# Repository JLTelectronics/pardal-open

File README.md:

<div align="center">

### Speed, speed cameras, matrix signs and road alerts from official open sources
**No account · No ads · No trip history**

-111)

</div>

---

Pardal is a calm co-pilot for the car. It shows your speed and the limit, warns you for speed cameras,
matrix signs and incidents on the road, and lets drivers warn each other — all from official open data,
without an account, without ads and without keeping track of where you drive.

<div align="center">

<table border="0" cellpadding="8">
<tr>
<td align="center"></td>
<td align="center"></td>
<td align="center"></td>
<td align="center"></td>
</tr>
<tr>
<td align="center" width="205"><sub>The meter at the top, and below it everything coming your way on the road.</sub></td>
<td align="center" width="205"><sub>Navigation with spoken directions, arrival time and the road's limit.</sub></td>
<td align="center" width="205"><sub>The map across the whole screen, with a large REPORT button.</sub></td>
<td align="center" width="205"><sub>Navigating between real buildings with their height from 3D BAG.</sub></td>
</tr>
</table>

</div>

## Why Pardal?

Speed-camera and traffic apps have grown ever more crowded, more expensive and more nosy:
subscriptions, accounts, ads and extensive tracking. Pardal is the opposite — a calm
co-pilot that does exactly what is needed and otherwise leaves you in peace.

| | |
|---|---|
| 🟠 **Useful from the very first metre** | The basics come from official open government data, so it is useful right away — even without a large user base. |
| 🟠 **Privacy by design** | No account, no trip history. Shared reports use a rotating, hashed device ID and a position rounded to ~1 km. |
| 🟠 **Calm on screen** | One clear meter, one quiet beep. Nothing that flashes or pops up unless your safety requires it. |
| 🟠 **Open and self-hostable** | The server, the hardware and the boot system are open source. |

## Features

| | |
|---|---|
| **Speed** | Large meter with the applicable limit; a calm warning when you go too fast. |
| **Speed cameras** | Fixed cameras, average-speed (section) controls and ANPR from OpenStreetMap. |
| **Matrix signs** | Live speeds and red crosses (lane closures) from NDW/Rijkswaterstaat. |
| **Road alerts** | Traffic jams, accidents, roadworks, closures and open bridges. |
| **Weather** | KNMI warnings along the way. |
| **Report it yourself** | Police, traffic jam, accident and more — visible to others after three confirmations. |
| **Navigation** | Address search, spoken directions in six languages and automatic re-routing. |
| **Offline map** | 2D/3D map from the Rijkswaterstaat road dataset; no data usage on the road. |
| **Multilingual** | Nederlands, English, Deutsch, Español, Português and Frysk. Light/dark theme. |

Full description: **[docs/FUNCTIES.md](docs/FUNCTIES.md)**.

## Where does it run?

| Platform | Status | |
|---|---|---|
| **iPhone** | ✅ Available, including **CarPlay** | [**Download on the App Store →**](https://apps.apple.com/nl/app/pardal/id6836411492) |
| **Android** | 🚧 On the way, including **Android Auto** | Coming to Google Play |
| **Dedicated car display** | 🚧 Open hardware in development | See [`hardware/`](hardware) and [the end of this page](#running-pardal-on-a-dash01) |

> The Pardal **apps** (iOS, Android) are proprietary and not part of this repository. This repository
> contains the open **server**, **hardware** and **DASH boot system**.

## Privacy

- No account, no ads, no analytics from third parties.
- Your location stays on your device. Only when you share a report does a position go to the server,
  rounded to ~1 km and kept in memory only.
- Device IDs are random and stored hashed; a report becomes visible to others only after three
  independent confirmations.

Details: [privacy statement](docs/play/privacyverklaring.md).

## Data sources

Rijkswaterstaat (WKD, matrix signs), NDW (traffic alerts), KNMI (weather) and OpenStreetMap
(speed cameras, roads) — supplemented with open data from several European countries. Details in
[docs/FUNCTIES.md](docs/FUNCTIES.md#data-sources).

## Self-hosting the server

Shared reports, the live map and navigation run through a small, open backend:

```sh
cd server
docker compose up -d --build
```

Configuration and optional receivers: [server/README.md](server/README.md).

## Open hardware

We are designing a round, standalone car display — a "phone without a camera" for the dashboard — with a
bootloader you can **always unlock and recover**. Open KiCad design and a complete bill of materials:
see [`hardware/`](hardware).

## Repository structure

| Folder | Contents |
|---|---|
| [`server/`](server) | Self-hostable backend (FastAPI + SQLite): shared reports, live map, navigation, app configuration. |
| [`hardware/`](hardware) | Open hardware for a round car display: KiCad PCB and bill of materials. |
| [`dash-pure/`](dash-pure) | Boot system and installer for running Pardal on a DASH01. |
| [`docs/`](docs) | Features, server configuration, installation guide and screenshots. |

## Community

Want to think along, help build, or just ride along and report what went wrong? You are welcome.

- 💬 **[Discord](https://discord.gg/HdaQD6NHMN)** — chat, help and ride-alongs
- 🐛 **[GitHub Issues](../../issues)** and **[Discussions](../../discussions)** — questions, ideas, bugs
- 🤝 **[CONTRIBUTING.md](CONTRIBUTING.md)** · **[ROADMAP.md](ROADMAP.md)** — `good first issue` is a nice place to start

---

## Running Pardal on a DASH01

<div align="center">
<table border="0" cellpadding="8">
<tr>
<td align="center"></td>
<td align="center"></td>
<td align="center"></td>
</tr>
</table>
</div>

The Flitsmeister DASH01 is designed to be used with a Flitsmeister subscription. With a small custom boot system and Android 13, your own hardware can run as a standalone on-board computer: **ignition on → Pardal logo → Pardal**, with no detours.

### Connectivity (4G, Wi-Fi & Bluetooth)

Pardal uses standard Android networking for live traffic alerts and map updates. The installer does not touch the built-in eSIM chip. Without an active Flitsmeister subscription, the built-in eSIM profile still shows the network operator but no longer provides mobile data. To get online, choose one of these:

* **Your own data eSIM:** add a data eSIM profile from a provider of your choice.
* **Wi-Fi hotspot:** connect the DASH01 to your phone's personal hotspot.
* **Bluetooth tethering:** share your phone's internet connection over Bluetooth.

Without a connection, Pardal keeps working with the most recently downloaded maps and speed cameras. As soon as it is online again (eSIM, Wi-Fi or Bluetooth), it updates to the latest speed cameras, road alerts and shared reports.

### Your device, your backup

The installer **first makes a complete, verified backup** of your own device and can
restore it to the factory state. **No factory firmware or Flitsmeister software is distributed**
— the installer uses only what is already on your own device, and the Android image (LineageOS GSI)
is downloaded by you from its official source.

→ [Installation guide](docs/DASH01-INSTALLEREN.md) · [How installation works](docs/BOOTLOADER.md) · [`dash-pure/`](dash-pure)

## Independence, trademarks & licence

Pardal is an **independent project**. It is not affiliated with, endorsed by or sponsored by
Flitsmeister or any other company. "Flitsmeister" and "DASH01" are names/trademarks of their
respective owners and are used here only to describe which hardware Pardal can run on.

This repository contains **no** code, firmware, data, APIs or other materials from Flitsmeister.
Installing Pardal on a device you own is your own choice and at your own risk: it can void your
warranty, and the original software and services will not work while Pardal is installed.
The software is provided **without any warranty**, as described in the licence.

### Licences

| Part | Licence |
|---|---|
| [`server/`](server) | [GNU AGPLv3](server/LICENSE) — if you run a modified version as a public service, you must share its source code. |
| [`hardware/`](hardware) | [CERN-OHL-S-2.0](hardware/LICENSE) — modified designs you make or distribute must be published under the same licence. |
| Everything else ([`dash-pure/`](dash-pure), [`docs/`](docs), ...) | [GNU GPLv3](LICENSE) |

Third-party components keep their own licences (see e.g. [`server/app/static/vendor/LICENSES.txt`](server/app/static/vendor/LICENSES.txt)).

The **Pardal name and logo** are not covered by these licences. You may not use them for your own
version or product without permission.

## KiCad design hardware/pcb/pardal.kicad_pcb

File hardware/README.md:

# Pardal hardware

Open hardware for a round, standalone car display: a "phone without a camera" for the dashboard, with a
bootloader you can **always unlock and recover**. Status: in development (rev B), not yet produced.

## Overview
- **Compute:** Radxa CM3 (Rockchip RK3566), Android 11/12 (Treble, GSIs run), open U-Boot.
- **Mobile:** Quectel EC200U-EU (LTE Cat 1 + GNSS), nano-SIM and a soldered eUICC (eSIM).
- **Screen:** round DSI display with touch.
- **Other:** speaker amplifier, vibration motor, side buttons, USB-C (power + data), optional Qi charging.

## Folder layout
| Folder | Contents |
|---|---|
| `pcb/` | KiCad project (`pardal.kicad_pro`), PCB renders and the generator scripts in `pcb/tools/`. |
| `pcb/libs/` | Symbols, footprints and 3D models used by the project. The `lcsc.*` libraries were generated from the LCSC/EasyEDA part library with [easyeda2kicad](https://github.com/uPesy/easyeda2kicad.py). |
| `pcb/datasheets/` | Pin tables (JSON) used by the generator scripts. |
| `pcb/tools/maten.py` | Board size and component positions (mm) used by `gen_pcb.py`. |

## PCB
Open `pcb/pardal.kicad_pro` in KiCad.

- Bill of materials with order numbers: [`pcb/ONDERDELEN.md`](pcb/ONDERDELEN.md).
- Layer stack-up, net classes and routing order: [`pcb/ROUTEREN.md`](pcb/ROUTEREN.md).

The schematic and board outline are generated from code. Run the scripts that use `pcbnew` with KiCad's Python:

```sh
cd pcb
python3 tools/gen_sch.py     # schematic sheets from tools/design.py
python3 tools/gen_pcb.py     # board outline, mounting holes, antenna zones, placement
python3 tools/regels.py      # net classes and design rules
python3 tools/route.py       # optional: autorouting with Freerouting
python3 tools/jlc.py "<part>"   # look up price/stock at JLCPCB/LCSC
```

Datasheets of the modules (Radxa, Quectel, …) are not included: download them from the manufacturers.

## Unlockable and unbrickable by design
- The secure-boot fuses are **never** blown: the chip always accepts your own bootloader.
- **Recovery button** behind a pinhole: hold it at power-on for Rockusb/Loader mode. Empty or broken storage
  falls back to Maskrom automatically. Flash with `rkdeveloptool` over USB-C.
- Debug UART and reset on test points.

See also [docs/BOOTLOADER.md](../docs/BOOTLOADER.md).

## Licence
The hardware design is licensed under the [CERN Open Hardware Licence v2 – Strongly Reciprocal](LICENSE)
(CERN-OHL-S-2.0). Source location: <https://github.com/JLTelectronics/pardal-open/tree/main/hardware>.
The scripts in `pcb/tools/` are part of the design source. The Pardal name and logo are not covered by this licence.

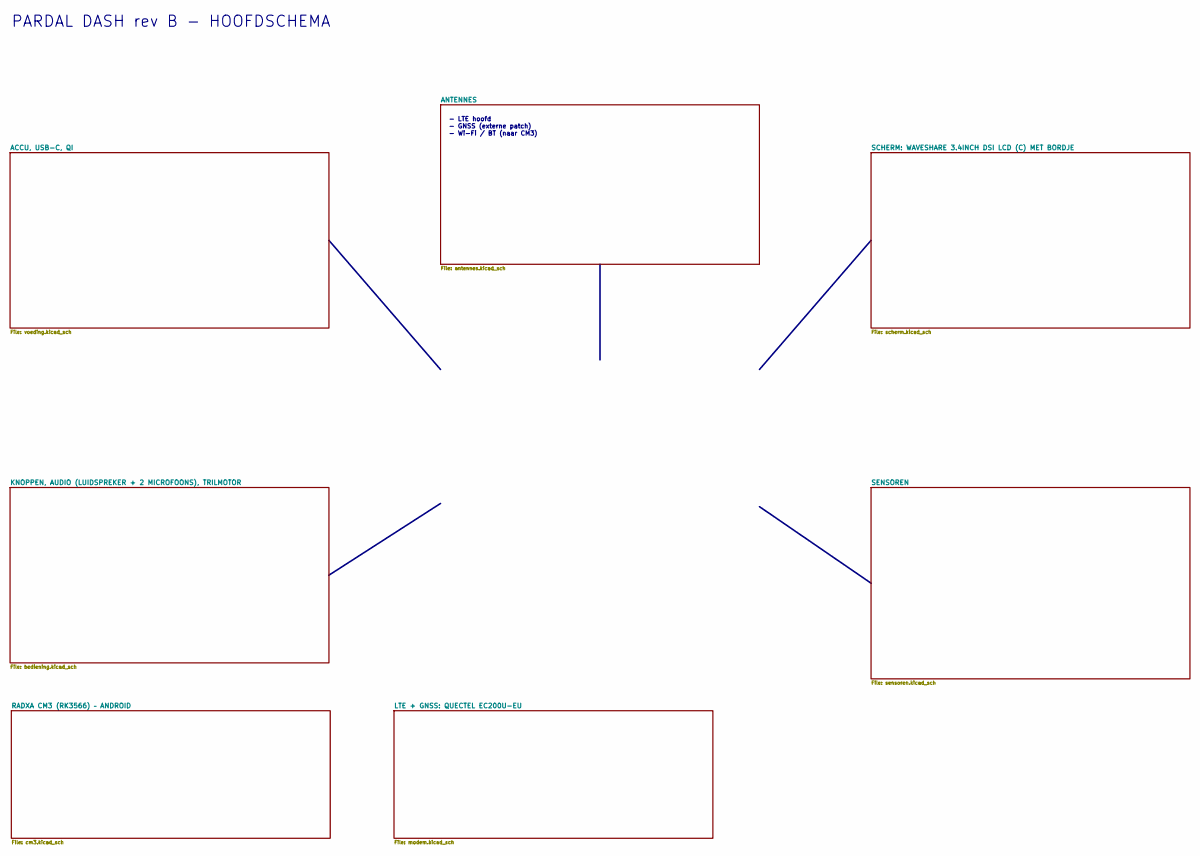
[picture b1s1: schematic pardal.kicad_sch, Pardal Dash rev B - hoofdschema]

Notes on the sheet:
- LTE hoofd - GNSS (externe patch) - Wi-Fi / BT (naar CM3)
PARDAL DASH rev B - HOOFDSCHEMA

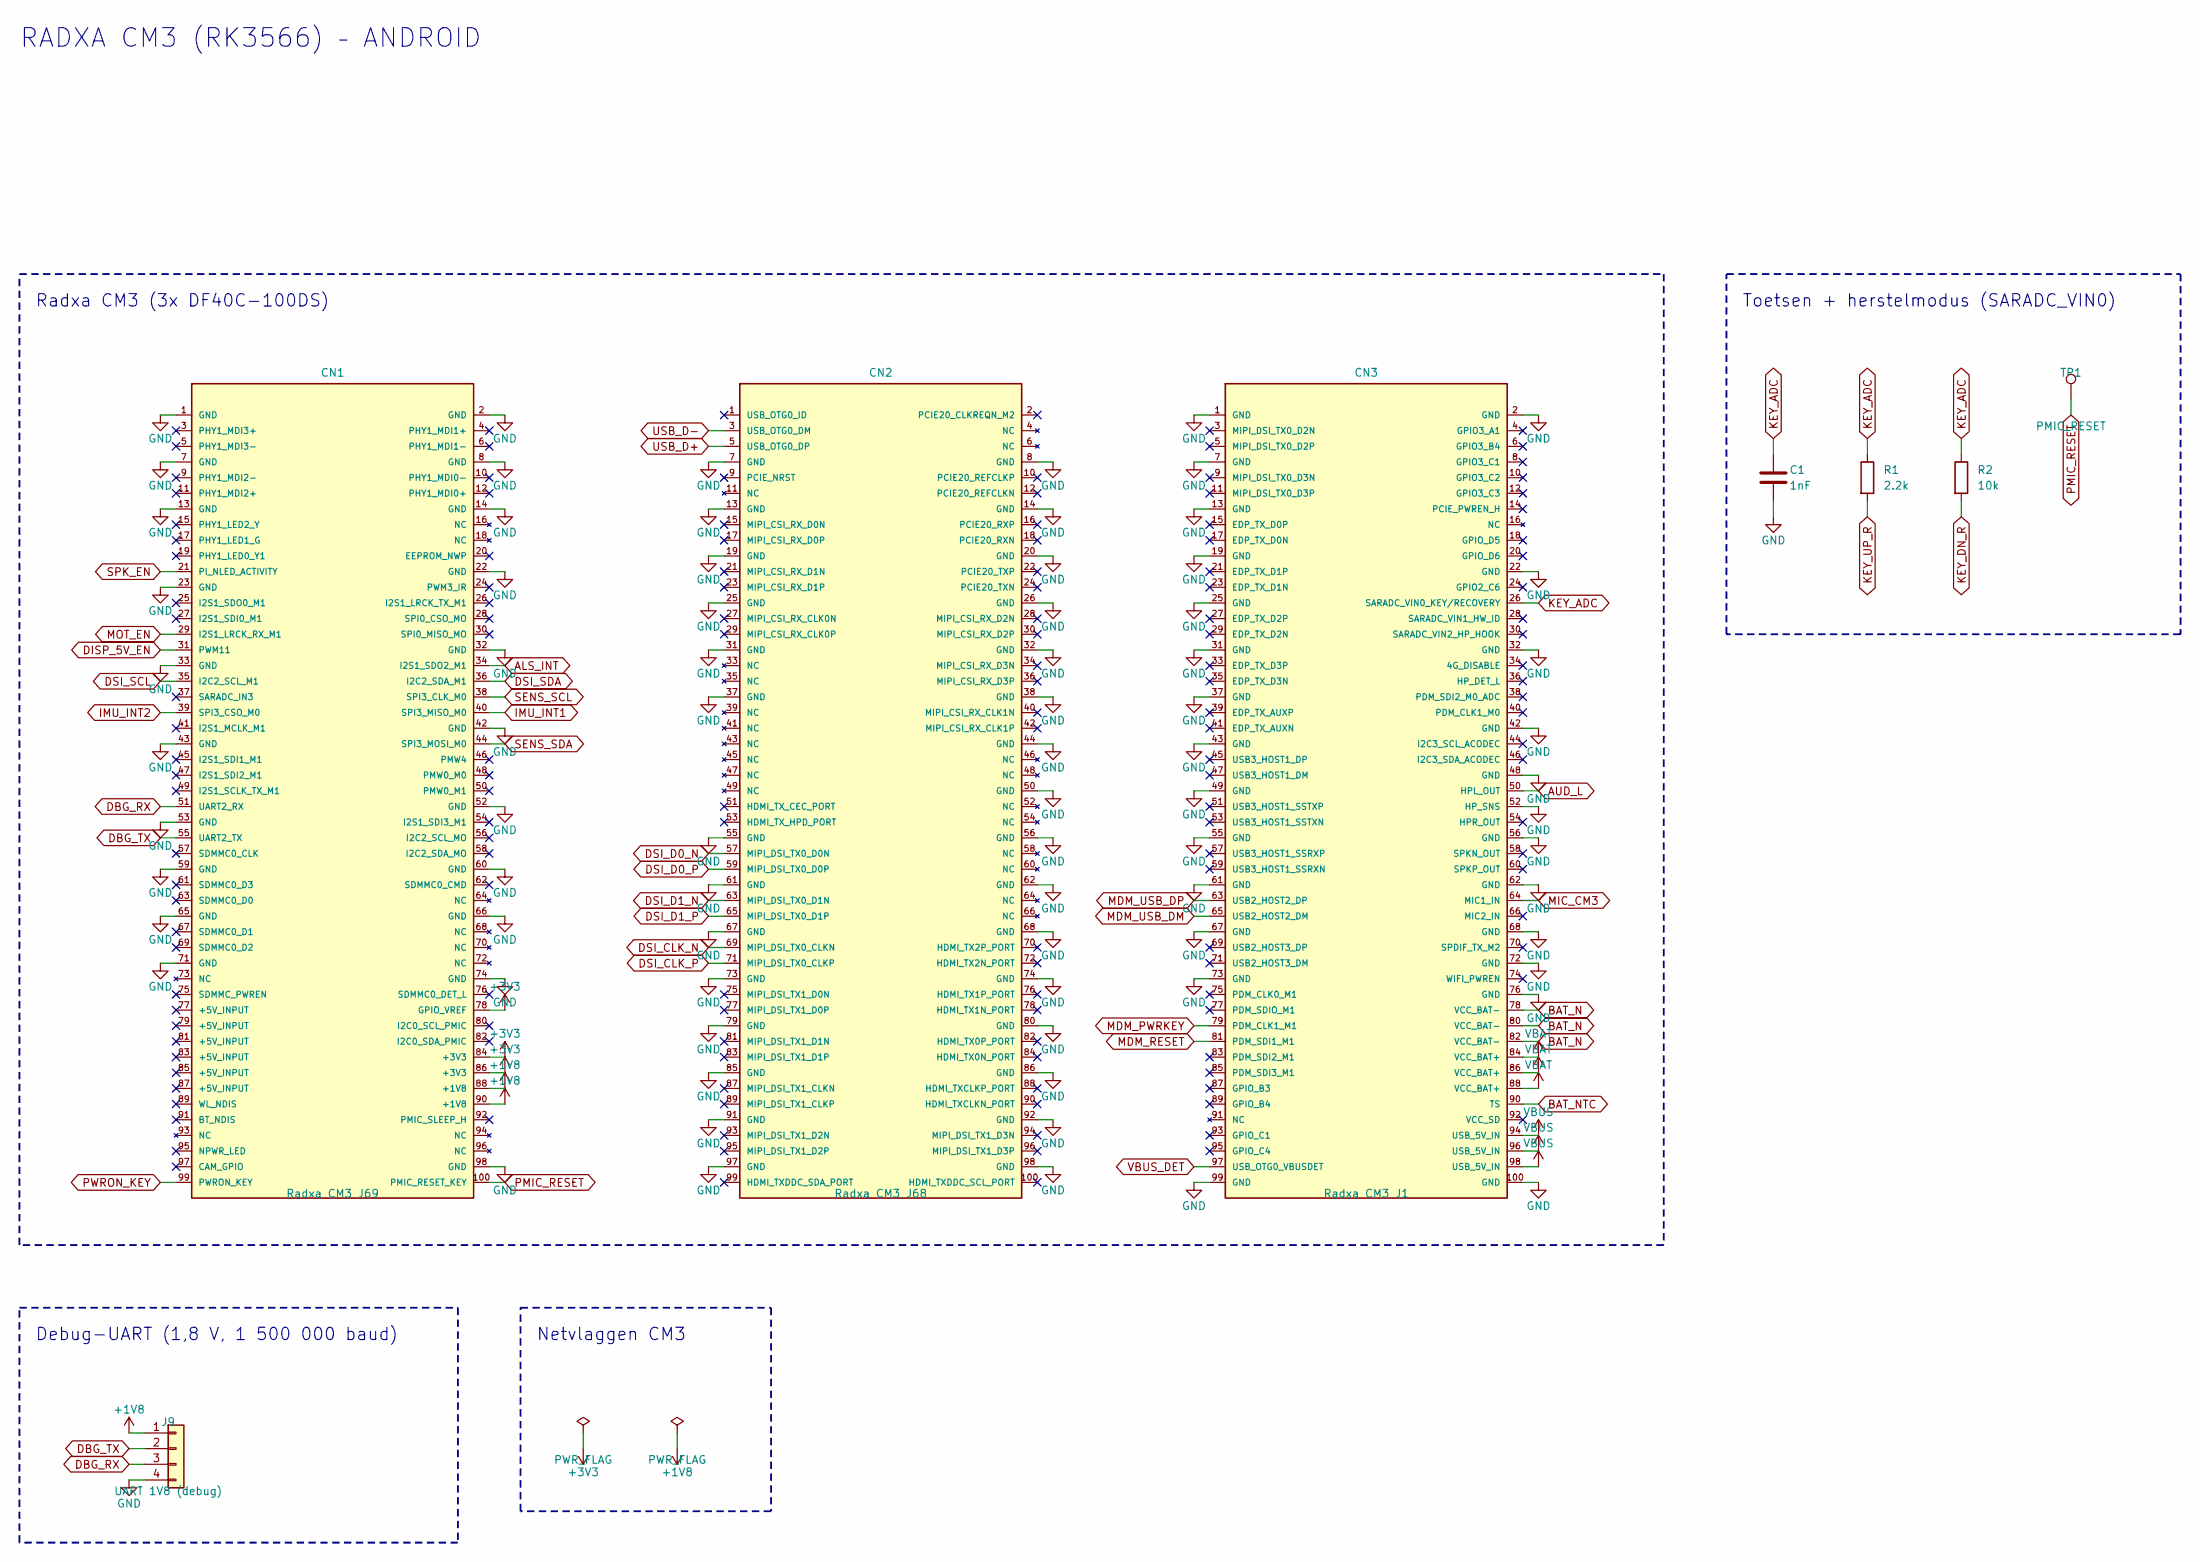
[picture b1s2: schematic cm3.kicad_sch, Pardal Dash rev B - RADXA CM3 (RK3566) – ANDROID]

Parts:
C1: 1nF; C_0402_1005Metric; LCSC C1523
CN1: Radxa CM3 J69; Radxa_CM3_J69; LCSC C597931
CN2: Radxa CM3 J68; Radxa_CM3_J68; LCSC C597931
CN3: Radxa CM3 J1; Radxa_CM3_J1; LCSC C597931
J9: UART 1V8 (debug); UART_4pads_P2.54
R1: 2.2k; R_0402_1005Metric; LCSC C25879
R2: 10k; R_0402_1005Metric; LCSC C25744
TP1: PMIC_RESET; TestPoint_Pad_D1.0mm

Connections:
+1V8: CN1.88 (+1V8), CN1.90 (+1V8), J9.1
+3V3: CN1.78 (GPIO_VREF), CN1.84 (+3V3), CN1.86 (+3V3); also elsewhere on the board
ALS_INT: CN1.34 (I2S1_SDO2_M1); also elsewhere on the board
AUD_L: CN3.50 (HPL_OUT); also elsewhere on the board
BAT_N: CN3.78 (VCC_BAT-), CN3.80 (VCC_BAT-), CN3.82 (VCC_BAT-); also elsewhere on the board
BAT_NTC: CN3.90 (TS); also elsewhere on the board
DBG_RX: CN1.51 (UART2_RX), J9.3
DBG_TX: CN1.55 (UART2_TX), J9.2
DISP_5V_EN: CN1.31 (PWM11); also elsewhere on the board
DSI_CLK_N: CN2.69 (MIPI_DSI_TX0_CLKN); also elsewhere on the board
DSI_CLK_P: CN2.71 (MIPI_DSI_TX0_CLKP); also elsewhere on the board
DSI_D0_N: CN2.57 (MIPI_DSI_TX0_D0N); also elsewhere on the board
DSI_D0_P: CN2.59 (MIPI_DSI_TX0_D0P); also elsewhere on the board
DSI_D1_N: CN2.63 (MIPI_DSI_TX0_D1N); also elsewhere on the board
DSI_D1_P: CN2.65 (MIPI_DSI_TX0_D1P); also elsewhere on the board
DSI_SCL: CN1.35 (I2C2_SCL_M1); also elsewhere on the board
DSI_SDA: CN1.36 (I2C2_SDA_M1); also elsewhere on the board
GND: C1.2, CN1.1 (GND), CN1.2 (GND), CN1.7 (GND), CN1.8 (GND), CN1.13 (GND), CN1.14 (GND), CN1.22 (GND), CN1.23 (GND), CN1.32 (GND), CN1.33 (GND), CN1.42 (GND), CN1.43 (GND), CN1.52 (GND), CN1.53 (GND), CN1.59 (GND), CN1.60 (GND), CN1.65 (GND), CN1.66 (GND), CN1.71 (GND), CN1.74 (GND), CN1.98 (GND), CN2.7 (GND), CN2.8 (GND), CN2.13 (GND), CN2.14 (GND), CN2.19 (GND), CN2.20 (GND), CN2.25 (GND), CN2.26 (GND), CN2.31 (GND), CN2.32 (GND), CN2.37 (GND), CN2.38 (GND), CN2.44 (GND), CN2.50 (GND), CN2.55 (GND), CN2.56 (GND), CN2.61 (GND), CN2.62 (GND), CN2.67 (GND), CN2.68 (GND), CN2.73 (GND), CN2.74 (GND), CN2.79 (GND), CN2.80 (GND), CN2.85 (GND), CN2.86 (GND), CN2.91 (GND), CN2.92 (GND), CN2.97 (GND), CN2.98 (GND), CN3.1 (GND), CN3.2 (GND), CN3.7 (GND), CN3.13 (GND), CN3.19 (GND), CN3.22 (GND), CN3.25 (GND), CN3.31 (GND), CN3.32 (GND), CN3.37 (GND), CN3.42 (GND), CN3.43 (GND), CN3.48 (GND), CN3.49 (GND), CN3.52 (HP_SNS), CN3.55 (GND), CN3.56 (GND), CN3.61 (GND), CN3.62 (GND), CN3.67 (GND), CN3.68 (GND), CN3.72 (GND), CN3.73 (GND), CN3.76 (GND), CN3.99 (GND), CN3.100 (GND), J9.4; also elsewhere on the board
IMU_INT1: CN1.40 (SPI3_MISO_M0); also elsewhere on the board
IMU_INT2: CN1.39 (SPI3_CSO_M0); also elsewhere on the board
KEY_ADC: C1.1, CN3.26 (SARADC_VIN0_KEY/RECOVERY), R1.1, R2.1; also elsewhere on the board
KEY_DN_R: R2.2; also elsewhere on the board
KEY_UP_R: R1.2; also elsewhere on the board
MDM_PWRKEY: CN3.79 (PDM_CLK1_M1); also elsewhere on the board
MDM_RESET: CN3.81 (PDM_SDI1_M1); also elsewhere on the board
MDM_USB_DM: CN3.65 (USB2_HOST2_DM); also elsewhere on the board
MDM_USB_DP: CN3.63 (USB2_HOST2_DP); also elsewhere on the board
MIC_CM3: CN3.64 (MIC1_IN); also elsewhere on the board
MOT_EN: CN1.29 (I2S1_LRCK_RX_M1); also elsewhere on the board
PMIC_RESET: CN1.100 (PMIC_RESET_KEY), TP1.1
PWRON_KEY: CN1.99 (PWRON_KEY); also elsewhere on the board
SENS_SCL: CN1.38 (SPI3_CLK_M0); also elsewhere on the board
SENS_SDA: CN1.44 (SPI3_MOSI_M0); also elsewhere on the board
SPK_EN: CN1.21 (PI_NLED_ACTIVITY); also elsewhere on the board
USB_D+: CN2.5 (USB_OTG0_DP); also elsewhere on the board
USB_D-: CN2.3 (USB_OTG0_DM); also elsewhere on the board
VBAT: CN3.84 (VCC_BAT+), CN3.86 (VCC_BAT+), CN3.88 (VCC_BAT+); also elsewhere on the board
VBUS: CN3.94 (USB_5V_IN), CN3.96 (USB_5V_IN), CN3.98 (USB_5V_IN); also elsewhere on the board
VBUS_DET: CN3.97 (USB_OTG0_VBUSDET); also elsewhere on the board

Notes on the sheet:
RADXA CM3 (RK3566) – ANDROID
Radxa CM3 (3x DF40C-100DS)
Toetsen + herstelmodus (SARADC_VIN0)
Debug-UART (1,8 V, 1 500 000 baud)
Netvlaggen CM3

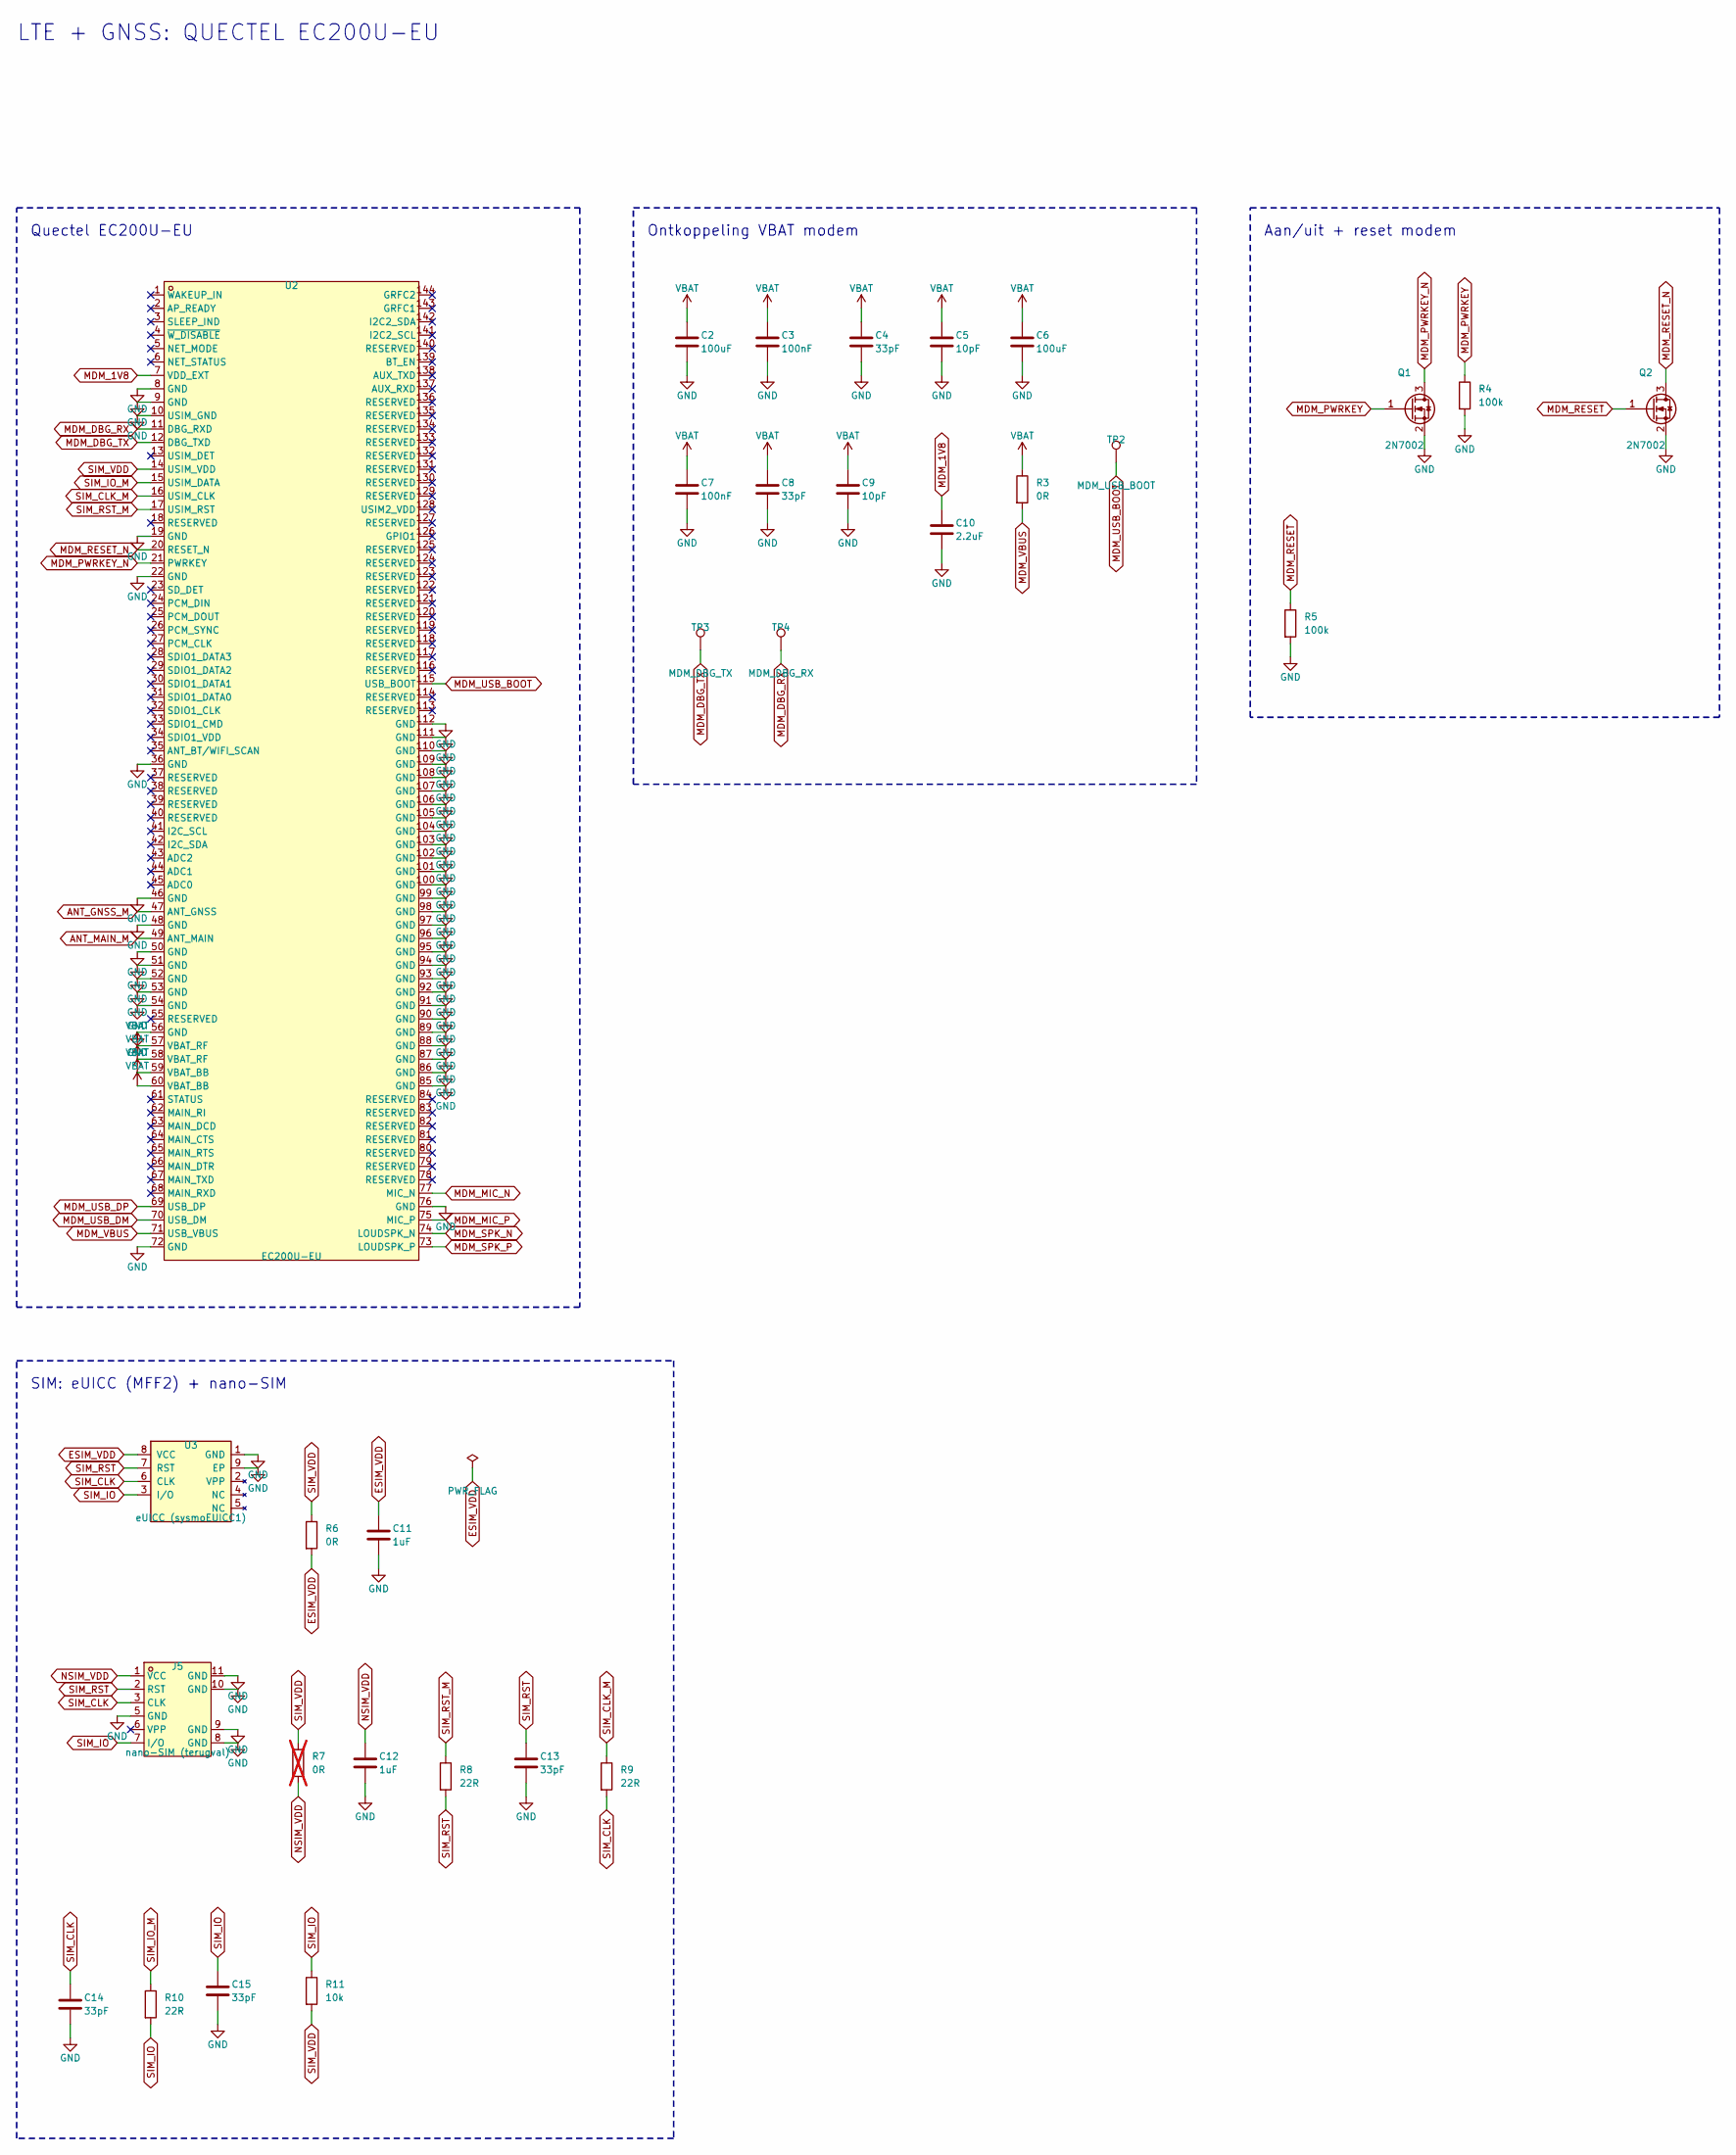
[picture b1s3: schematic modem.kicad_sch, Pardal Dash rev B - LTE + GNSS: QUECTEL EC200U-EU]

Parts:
C2, C6: 100uF; C_1206_3216Metric; LCSC C15008
C3, C7: 100nF; C_0402_1005Metric; LCSC C1525
C4, C8, C13, C14, C15: 33pF; C_0402_1005Metric; LCSC C1562
C5, C9: 10pF; C_0402_1005Metric; LCSC C32949
C10: 2.2uF; C_0603_1608Metric; LCSC C23630
C11, C12: 1uF; C_0402_1005Metric; LCSC C52923
J5: nano-SIM (terugval); SIM-SMD_NANO-SIM-XG6P-H1.35; LCSC C7529386
Q1, Q2: 2N7002; SOT-23; LCSC C8545
R3, R6: 0R; R_0402_1005Metric; LCSC C17168
R4, R5: 100k; R_0402_1005Metric; LCSC C25741
R7: 0R; R_0402_1005Metric; LCSC C17168; not fitted
R8, R9, R10: 22R; R_0402_1005Metric; LCSC C25092
R11: 10k; R_0402_1005Metric; LCSC C25744
TP2: MDM_USB_BOOT; TestPoint_Pad_D1.0mm
TP3: MDM_DBG_TX; TestPoint_Pad_D1.0mm
TP4: MDM_DBG_RX; TestPoint_Pad_D1.0mm
U2: EC200U-EU; LCC-LGA-144_L31.0-W28.0-P1.30_L610-CN-02; LCSC C2942341
U3: eUICC (sysmoEUICC1); DFN-8-1EP_6x5mm_P1.27mm_EP2x2mm

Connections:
ANT_GNSS_M: U2.47 (ANT_GNSS); also elsewhere on the board
ANT_MAIN_M: U2.49 (ANT_MAIN); also elsewhere on the board
ESIM_VDD: C11.1, R6.2, U3.8 (VCC)
GND: C2.2, C3.2, C4.2, C5.2, C6.2, C7.2, C8.2, C9.2, C10.2, C11.2, C12.2, C13.2, C14.2, C15.2, J5.5 (GND), J5.8 (GND), J5.9 (GND), J5.10 (GND), J5.11 (GND), Q1.2 (S), Q2.2 (S), R4.2, R5.2, U2.8 (GND), U2.9 (GND), U2.10 (USIM_GND), U2.19 (GND), U2.22 (GND), U2.36 (GND), U2.46 (GND), U2.48 (GND), U2.50 (GND), U2.51 (GND), U2.52 (GND), U2.53 (GND), U2.54 (GND), U2.56 (GND), U2.72 (GND), U2.76 (GND), U2.85 (GND), U2.86 (GND), U2.87 (GND), U2.88 (GND), U2.89 (GND), U2.90 (GND), U2.91 (GND), U2.92 (GND), U2.93 (GND), U2.94 (GND), U2.95 (GND), U2.96 (GND), U2.97 (GND), U2.98 (GND), U2.99 (GND), U2.100 (GND), U2.101 (GND), U2.102 (GND), U2.103 (GND), U2.104 (GND), U2.105 (GND), U2.106 (GND), U2.107 (GND), U2.108 (GND), U2.109 (GND), U2.110 (GND), U2.111 (GND), U2.112 (GND), U3.1 (GND), U3.9 (EP); also elsewhere on the board
MDM_1V8: C10.1, U2.7 (VDD_EXT)
MDM_DBG_RX: TP4.1, U2.11 (DBG_RXD)
MDM_DBG_TX: TP3.1, U2.12 (DBG_TXD)
MDM_MIC_N: U2.77 (MIC_N); also elsewhere on the board
MDM_MIC_P: U2.75 (MIC_P); also elsewhere on the board
MDM_PWRKEY: Q1.1 (G), R4.1; also elsewhere on the board
MDM_PWRKEY_N: Q1.3 (D), U2.21 (PWRKEY)
MDM_RESET: Q2.1 (G), R5.1; also elsewhere on the board
MDM_RESET_N: Q2.3 (D), U2.20 (RESET_N)
MDM_SPK_N: U2.74 (LOUDSPK_N); also elsewhere on the board
MDM_SPK_P: U2.73 (LOUDSPK_P); also elsewhere on the board
MDM_USB_BOOT: TP2.1, U2.115 (USB_BOOT)
MDM_USB_DM: U2.70 (USB_DM); also elsewhere on the board
MDM_USB_DP: U2.69 (USB_DP); also elsewhere on the board
MDM_VBUS: R3.2, U2.71 (USB_VBUS)
NSIM_VDD: C12.1, J5.1 (VCC), R7.2
SIM_CLK: C14.1, J5.3 (CLK), R9.2, U3.6 (CLK)
SIM_CLK_M: R9.1, U2.16 (USIM_CLK)
SIM_IO: C15.1, J5.7 (I/O), R10.2, R11.1, U3.3 (I/O)
SIM_IO_M: R10.1, U2.15 (USIM_DATA)
SIM_RST: C13.1, J5.2 (RST), R8.2, U3.7 (RST)
SIM_RST_M: R8.1, U2.17 (USIM_RST)
SIM_VDD: R6.1, R7.1, R11.2, U2.14 (USIM_VDD)
VBAT: C2.1, C3.1, C4.1, C5.1, C6.1, C7.1, C8.1, C9.1, R3.1, U2.57 (VBAT_RF), U2.58 (VBAT_RF), U2.59 (VBAT_BB), U2.60 (VBAT_BB); also elsewhere on the board

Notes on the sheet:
LTE + GNSS: QUECTEL EC200U-EU
Quectel EC200U-EU
Ontkoppeling VBAT modem
Aan/uit + reset modem
SIM: eUICC (MFF2) + nano-SIM

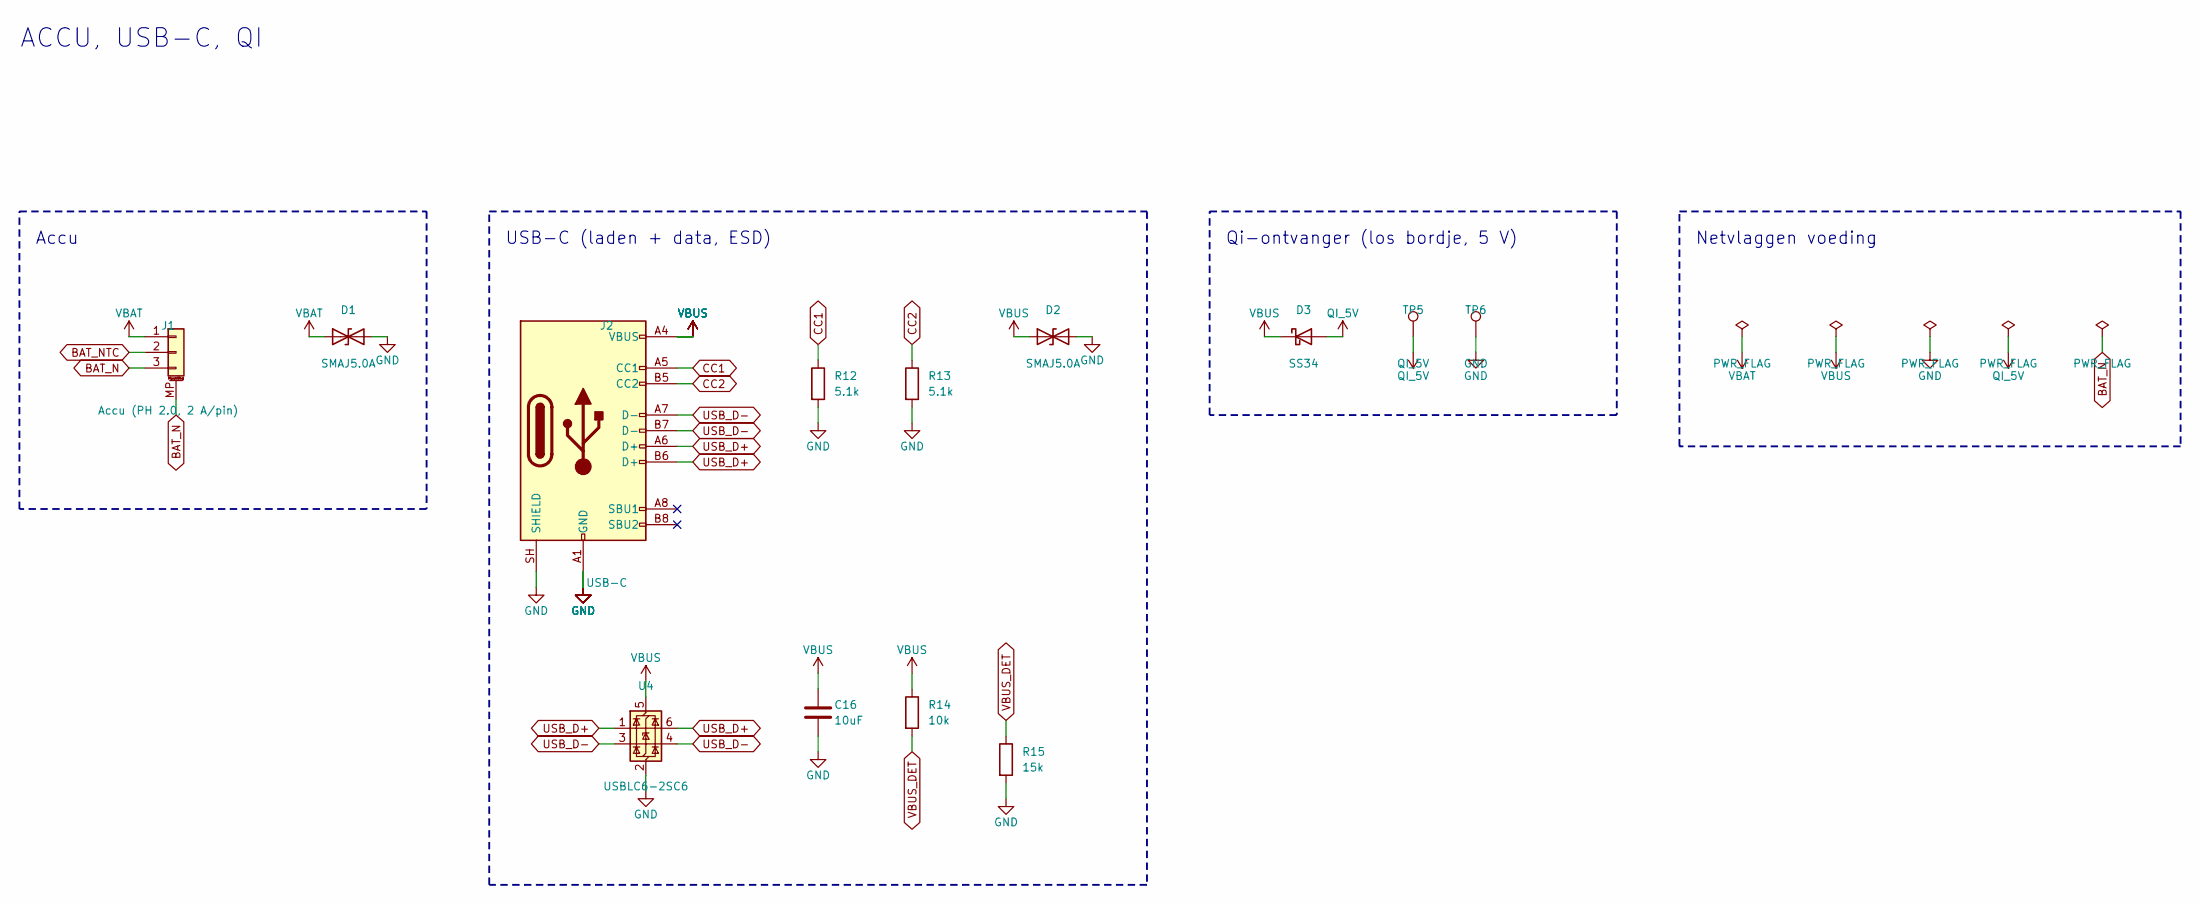
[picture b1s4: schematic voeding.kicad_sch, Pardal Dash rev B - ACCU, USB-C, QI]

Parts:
C16: 10uF; C_0603_1608Metric; LCSC C19702
D1, D2: SMAJ5.0A; D_SMA; LCSC C908757
D3: SS34; D_SMA; LCSC C8678
J1: Accu (PH 2.0, 2 A/pin); JST_PH_S3B-PH-SM4-TB_1x03-1MP_P2.00mm_Horizontal; LCSC C52025061
J2: USB-C; USB_C_Receptacle_HRO_TYPE-C-31-M-12; LCSC C165948
R12, R13: 5.1k; R_0402_1005Metric; LCSC C25905
R14: 10k; R_0402_1005Metric; LCSC C25744
R15: 15k; R_0402_1005Metric; LCSC C25756
TP5: QI_5V; TestPoint_Pad_2.0x2.0mm
TP6: GND; TestPoint_Pad_2.0x2.0mm
U4: USBLC6-2SC6; SOT-23-6; LCSC C2827654

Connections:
BAT_N: J1.3, J1.MP (MountPin); also elsewhere on the board
BAT_NTC: J1.2; also elsewhere on the board
CC1: J2.A5 (CC1), R12.1
CC2: J2.B5 (CC2), R13.1
GND: C16.2, D1.2 (A2), D2.2 (A2), J2.A1 (GND), J2.A12 (GND), J2.B1 (GND), J2.B12 (GND), J2.SH (SHIELD), R12.2, R13.2, R15.2, TP6.1, U4.2 (GND); also elsewhere on the board
QI_5V: D3.2 (A), TP5.1
USB_D+: J2.A6 (D+), J2.B6 (D+), U4.1 (I/O1), U4.6 (I/O1); also elsewhere on the board
USB_D-: J2.A7 (D-), J2.B7 (D-), U4.3 (I/O2), U4.4 (I/O2); also elsewhere on the board
VBAT: D1.1 (A1), J1.1; also elsewhere on the board
VBUS: C16.1, D2.1 (A1), D3.1 (K), J2.A4 (VBUS), J2.A9 (VBUS), J2.B4 (VBUS), J2.B9 (VBUS), R14.1, U4.5 (VBUS); also elsewhere on the board
VBUS_DET: R14.2, R15.1; also elsewhere on the board

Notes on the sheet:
ACCU, USB-C, QI
Accu
USB-C (laden + data, ESD)
Qi-ontvanger (los bordje, 5 V)
Netvlaggen voeding

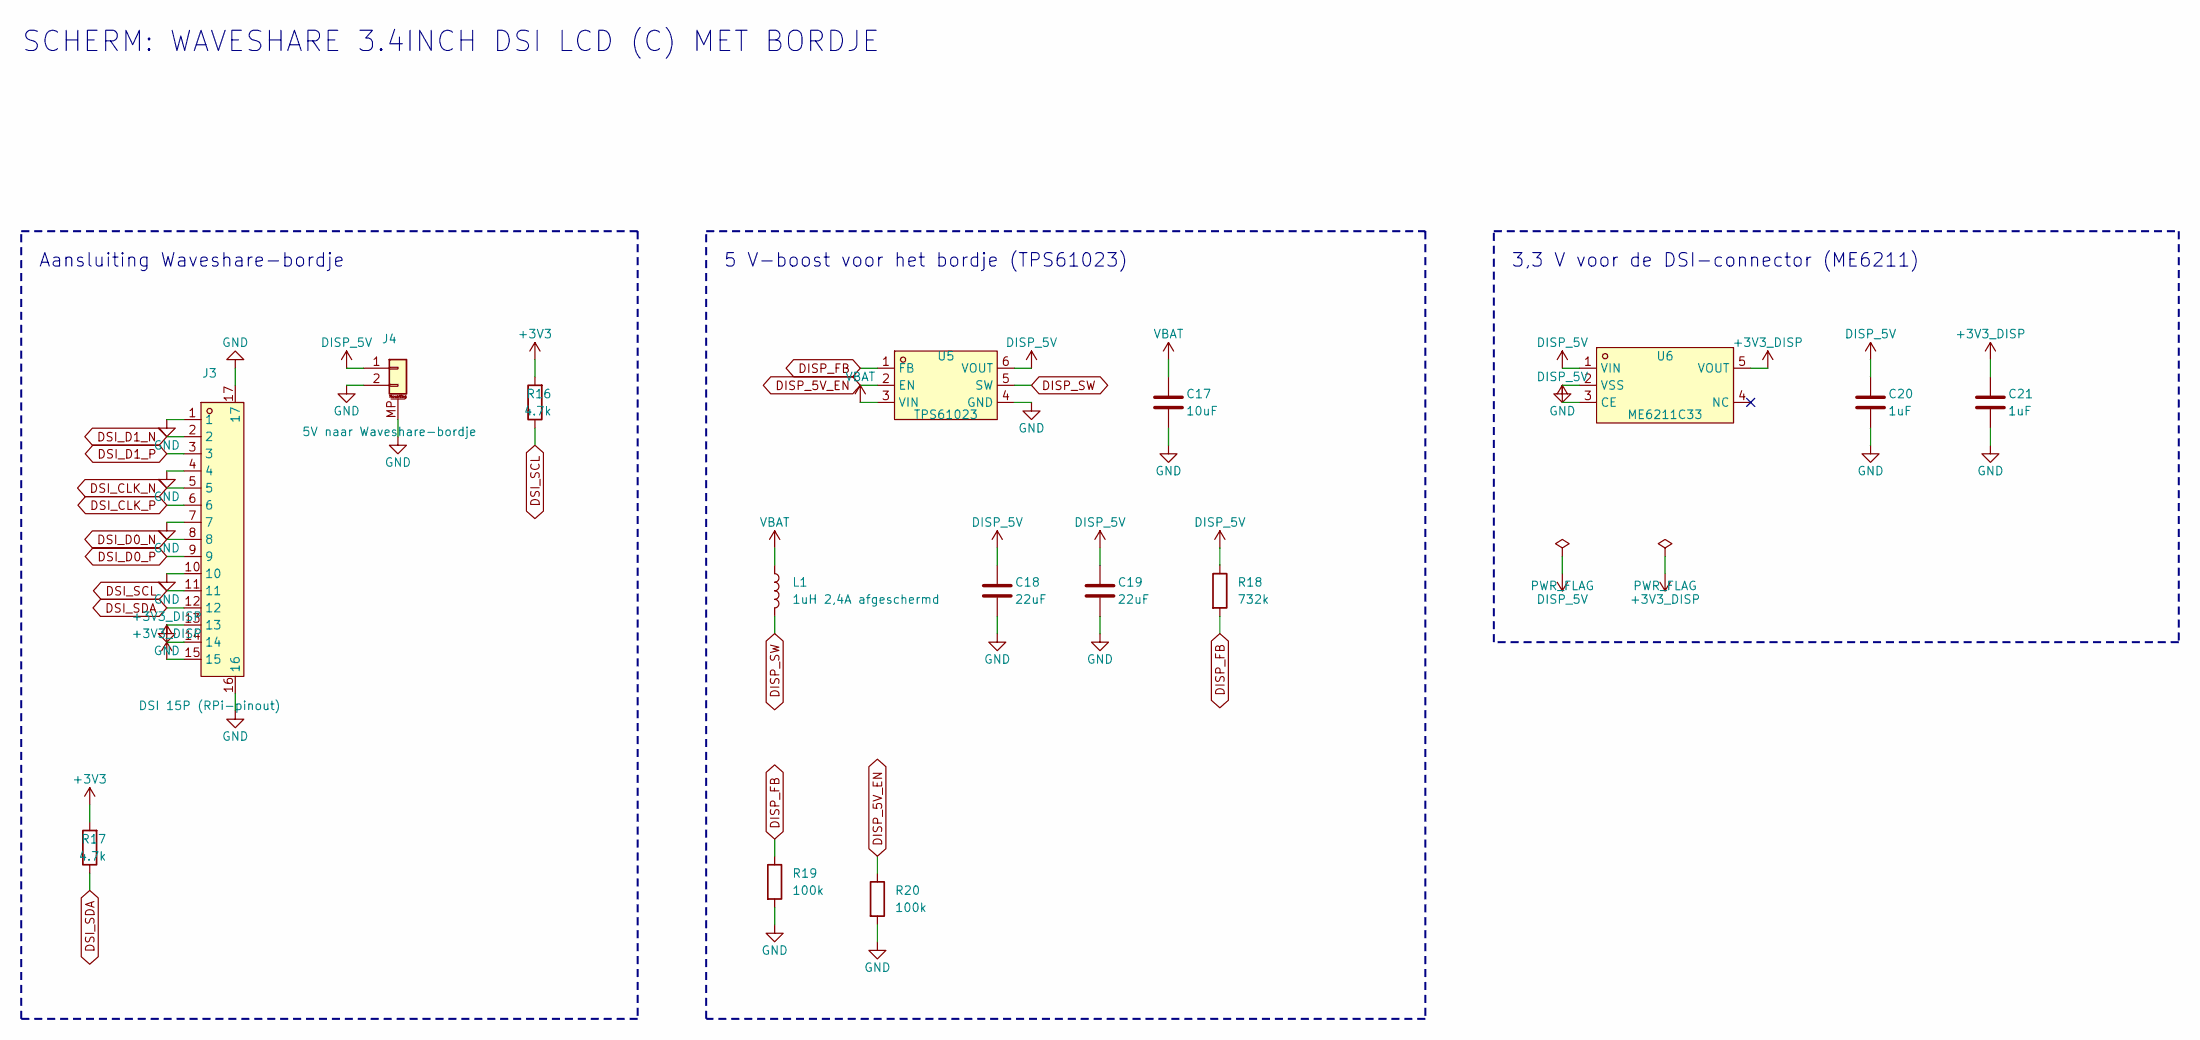
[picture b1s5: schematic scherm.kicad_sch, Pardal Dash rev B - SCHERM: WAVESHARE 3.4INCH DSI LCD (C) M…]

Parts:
C17: 10uF; C_0603_1608Metric; LCSC C19702
C18, C19: 22uF; C_0603_1608Metric; LCSC C59461
C20, C21: 1uF; C_0402_1005Metric; LCSC C52923
J3: DSI 15P (RPi-pinout); CONN-SMD_15P-P1.00_SHOU-HAN_1.0MM-15P-LT; LCSC C7529394
J4: 5V naar Waveshare-bordje; JST_SH_SM02B-SRSS-TB_1x02-1MP_P1.00mm_Horizontal; LCSC C19271996
L1: 1uH 2,4A afgeschermd; L_1008_2520Metric; LCSC C2849428
R16, R17: 4.7k; R_0402_1005Metric; LCSC C25900
R18: 732k; R_0402_1005Metric; LCSC C5159692
R19, R20: 100k; R_0402_1005Metric; LCSC C25741
U5: TPS61023; SOT-563_L1.6-W1.2-P0.50-LS1.6-BR; LCSC C919459
U6: ME6211C33; SOT-23-5_L3.0-W1.7-P0.95-LS2.8-BL; LCSC C82942

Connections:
+3V3: R16.2, R17.2; also elsewhere on the board
+3V3_DISP: C21.1, J3.14, J3.15, U6.5 (VOUT)
DISP_5V: C18.1, C19.1, C20.1, J4.1, R18.1, U5.6 (VOUT), U6.1 (VIN), U6.3 (CE)
DISP_5V_EN: R20.1, U5.2 (EN); also elsewhere on the board
DISP_FB: R18.2, R19.1, U5.1 (FB)
DISP_SW: L1.2, U5.5 (SW)
DSI_CLK_N: J3.5; also elsewhere on the board
DSI_CLK_P: J3.6; also elsewhere on the board
DSI_D0_N: J3.8; also elsewhere on the board
DSI_D0_P: J3.9; also elsewhere on the board
DSI_D1_N: J3.2; also elsewhere on the board
DSI_D1_P: J3.3; also elsewhere on the board
DSI_SCL: J3.11, R16.1; also elsewhere on the board
DSI_SDA: J3.12, R17.1; also elsewhere on the board
GND: C17.2, C18.2, C19.2, C20.2, C21.2, J3.1, J3.4, J3.7, J3.10, J3.13, J3.16, J3.17, J4.2, J4.MP (MountPin), R19.2, R20.2, U5.4 (GND), U6.2 (VSS); also elsewhere on the board
VBAT: C17.1, L1.1, U5.3 (VIN); also elsewhere on the board

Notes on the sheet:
SCHERM: WAVESHARE 3.4INCH DSI LCD (C) MET BORDJE
Aansluiting Waveshare-bordje
5 V-boost voor het bordje (TPS61023)
3,3 V voor de DSI-connector (ME6211)

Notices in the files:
README.md:
License: GPLv3 · AGPLv3 · CERN-OHL-S
